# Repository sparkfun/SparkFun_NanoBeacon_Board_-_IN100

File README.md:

SparkFun NanoBeacon Board - IN100
====================================
<table class="table table-hover table-striped table-bordered">
  <tr align="center">
    <td></td>
    <td></td>
   </tr>
   <tr align="center">
    <td><a href="https://www.sparkfun.com/products/21327">SparkFun NanoBeacon Board - IN100</a></td>
    <td><a href="https://www.sparkfun.com/products/21293">SparkFun NanoBeacon Lite Board - IN100
   </tr>
</table>

The [SparkFun NanoBeacon Board - IN100](https://www.sparkfun.com/products/21327) and [SparkFun NanoBeacon Lite Board - IN100](https://www.sparkfun.com/products/21293) offer a 2.4 GHz wireless low energy BT beacon breakout with exceptional low power consumption features and minimal programming required. The board features the IN100 NanoBeacon<sup>&trade;</sup> from InPlay<sup>&trade;</sup>. The IN100 SoC is compliant with several standard 2.4 GHz protocols and has several built-in configurable features for device behavior that can drastically reduce power consumption allowing for continuous operation in the field for multiple years even with a connected device. The two versions all for users to prototype with the Lite (Development) version and then employ the standard (Production) version in large installation once your hardware and software design is complete. The board features the IN100 NanoBeacon<sup>&trade;</sup> from InPlay<sup>&trade;</sup>. The NanoBeacon config tool allows for software-free programming of the modules removing any need to perform any tricky programming for sending and receiving packets.

Repository Contents
-------------------

* **/Documents** - Datasheets, additional user documents
* **/Examples** - IN100 Config and Arduino example
* **/Hardware** - Eagle design files (.brd, .sch)
* **/Production** - Production panel files (.brd)

Documentation
--------------
* **[SparkFun NanoBeacon Board - IN100 Hookup Guide](https://learn.sparkfun.com/tutorials/sparkfun-nanobeacon-board---in100-hookup-guide)** - Basic Hookup Guide for the NanoBeacon boards.

Product Versions
-----------------

* [WRL-21327](https://www.sparkfun.com/products/21327) - NanoBeacon Board initial release (includes headers)
* [WRL-21293](https://www.sparkfun.com/products/21293) - NanoBeacon Lite Board initial release (includes Reset button and Power LED)

License Information
-------------------

This product is _**open source**_! 

Please review the LICENSE.md file for license information. 

If you have any questions or concerns on licensing, please contact technical support on our [SparkFun forums](https://forum.sparkfun.com/viewforum.php?f=152).

Distributed as-is; no warranty is given.

- Your friends at SparkFun.

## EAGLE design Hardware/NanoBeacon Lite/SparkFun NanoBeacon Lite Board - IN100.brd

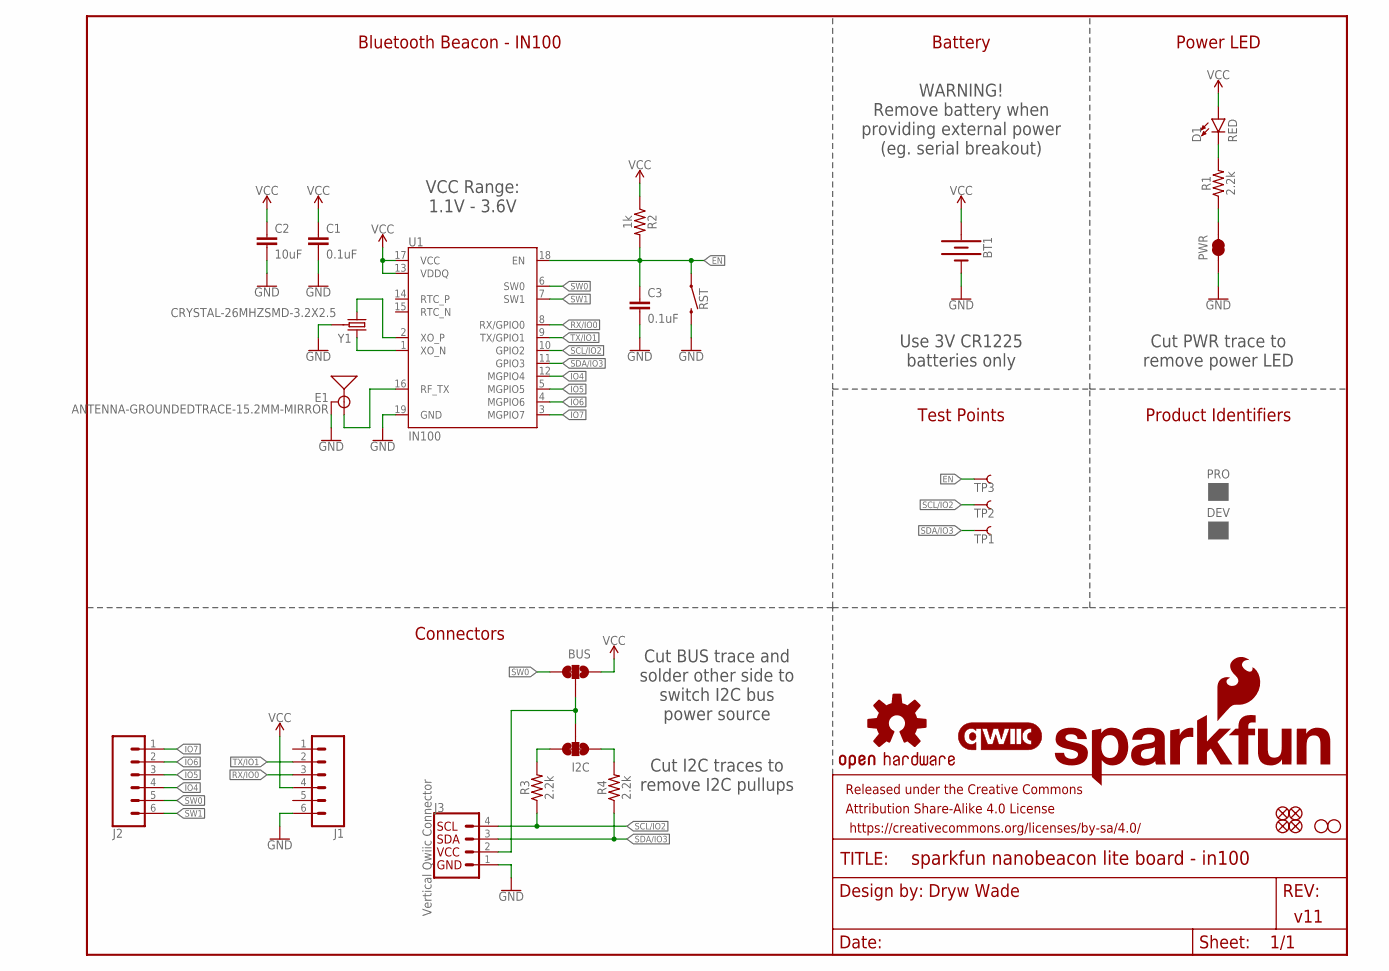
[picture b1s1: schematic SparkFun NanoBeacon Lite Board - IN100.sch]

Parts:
BT1: BATTERY-12MM_SMD_BOTH_PWR_PADS; BATTCON_12MM
BUS: JUMPER-SMT_3_1-NC_TRACE_SILK; SMT-JUMPER_3_1-NC_TRACE_SILK
C1, C3: 0.1uF; 0402-TIGHT
C2: 10uF; 0402-TIGHT
D1: RED; LED-0402
DEV: PROD_ID_PASTE_SILK; PRODUCT_IDENT_PASTE_SILK
E1: ANTENNA-GROUNDEDTRACE-15.2MM-MIRROR; TRACE_ANTENNA_2.4GHZ_15.2MM_MIRROR
FD1, FD2, FD3, FD4: FIDUCIAL1X2; FIDUCIAL-1X2
FRAME1: FRAME-LETTER; CREATIVE_COMMONS
H1, H2: STAND-OFF
I2C: JUMPER-SMT_3_2-NC_TRACE_SILK; SMT-JUMPER_3_2-NC_TRACE_SILK
J1, J2: CONN_06NO_SILK_NO_POP; 1X06_NO_SILK
J3: Vertical Qwiic Connector; JST04_1MM_VERT
LOGO1: OSHW-LOGOS; OSHW-LOGO-S
LOGO2: SFE_LOGO_NAME_FLAME.1_INCH; SFE_LOGO_NAME_FLAME_.1
LOGO3: QWIIC_LOGO_5MM; QWIIC_5MM
PRO: PROD_ID_PASTE_SILK; PRODUCT_IDENT_PASTE_SILK
PWR: JUMPER-SMT_2_NC_TRACE_SILK; SMT-JUMPER_2_NC_TRACE_SILK
R1, R3, R4: 2.2k; 0402-TIGHT
R2: 1k; 0402-TIGHT
RST: MOMENTARY-SWITCH-SPST-SMD-4.6X2.8MM; TACTILE_SWITCH_SMD_4.6X2.8MM
TP1, TP2, TP3: TEST-POINT3; PAD.03X.03
U1: IN100
Y1: CRYSTAL-26MHZSMD-3.2X2.5; CRYSTAL-SMD-3.2X2.5MM

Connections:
EN: C3.1, R2.2, RST.1, RST.2 (1), TP3.1, U1.18 (EN)
GND: BT1.GND (-), C1.2, C2.2, C3.2, E1.GND, J1.6, J3.1, PWR.1, RST.3 (2), RST.4 (2), U1.19 (GND), Y1.2 (GND), Y1.4 (GND)
IO4: J2.4, U1.12 (MGPIO4)
IO5: J2.3, U1.5 (MGPIO5)
IO6: J2.2, U1.4 (MGPIO6)
IO7: J2.1, U1.3 (MGPIO7)
unnamed: U1.1 (XO_N), Y1.3 (2)
unnamed: U1.2 (XO_P), Y1.1
unnamed: PWR.2, R1.1
unnamed: E1.ANT (SIGNAL), U1.16 (RF_TX)
unnamed: D1.C, R1.2
unnamed: I2C.1, R4.2
unnamed: BUS.2, I2C.2, J3.2
unnamed: I2C.3, R3.2
RX/IO0: J1.3, U1.8 (RX/GPIO0)
SCL/IO2: J3.4, R3.1, TP2.1, U1.10 (GPIO2)
SDA/IO3: J3.3, R4.1, TP1.1, U1.11 (GPIO3)
SW0: BUS.3, J2.5, U1.6 (SW0)
SW1: J2.6, U1.7 (SW1)
TX/IO1: J1.2, U1.9 (TX/GPIO1)
VCC: BT1.PWR@1 (+), BT1.PWR@2 (+), BUS.1, C1.1, C2.1, D1.A, J1.4, R2.1, U1.13 (VDDQ), U1.17 (VCC)

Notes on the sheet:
v11
Dryw Wade
Connectors
Battery
Bluetooth Beacon - IN100
Power LED
Cut PWR trace to remove power LED
VCC Range: 1.1V - 3.6V
Test Points
Cut I2C traces to remove I2C pullups
Cut BUS trace and solder other side to switch I2C bus power source
Use 3V CR1225 batteries only
WARNING\! Remove battery when providing external power (eg. serial breakout)
Product Identifiers

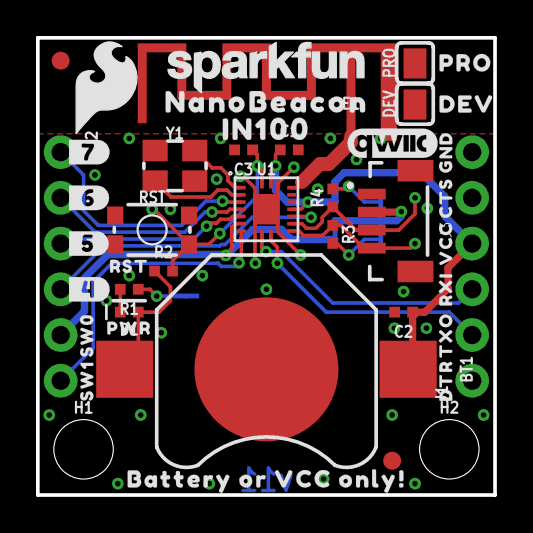
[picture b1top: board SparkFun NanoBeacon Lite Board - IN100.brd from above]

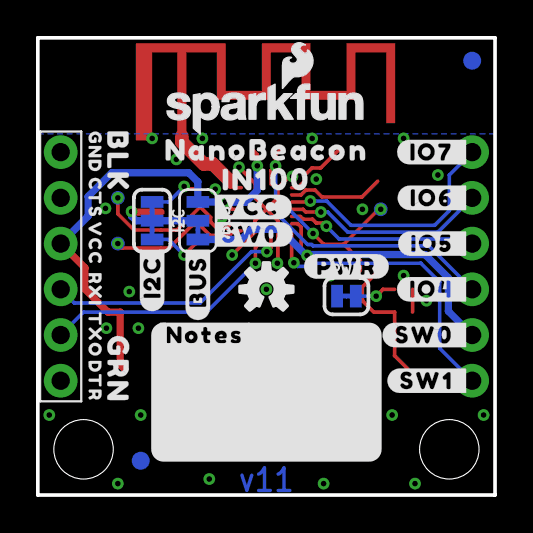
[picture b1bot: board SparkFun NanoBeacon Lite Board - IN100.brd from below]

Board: 2 copper layers, 25.4 x 25.4 mm, 63 parts (24 on the bottom side), 21 nets.

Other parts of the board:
U$1, U$29: NANOBEACON0
U$2: #_7#0
U$3: #_6#0
U$4: SFE_LOGO_NAME_.1
U$5, U$31: IN1000
U$6: #_5#0
U$7: #_4#0
U$8: SFE_LOGO_FLAME_.2
U$9: BATTERY_OR_VCC_ONLY##0
U$11: #I2C#0
U$12: #NOTES#0
U$13: #IO7_#0
U$14: #IO6_#0
U$15: #IO5_#0
U$16: #IO4_#0
U$17: #SW0_#0
U$18: #SW1_#0
U$19: #PWR#0
U$20: #SW0#3
U$21: SW00
U$22: SW10
U$23: RST0
U$24: #VCC#0
U$25: #BUS#0
U$26: PWR0
U$28: DEV0
U$30: PRO0

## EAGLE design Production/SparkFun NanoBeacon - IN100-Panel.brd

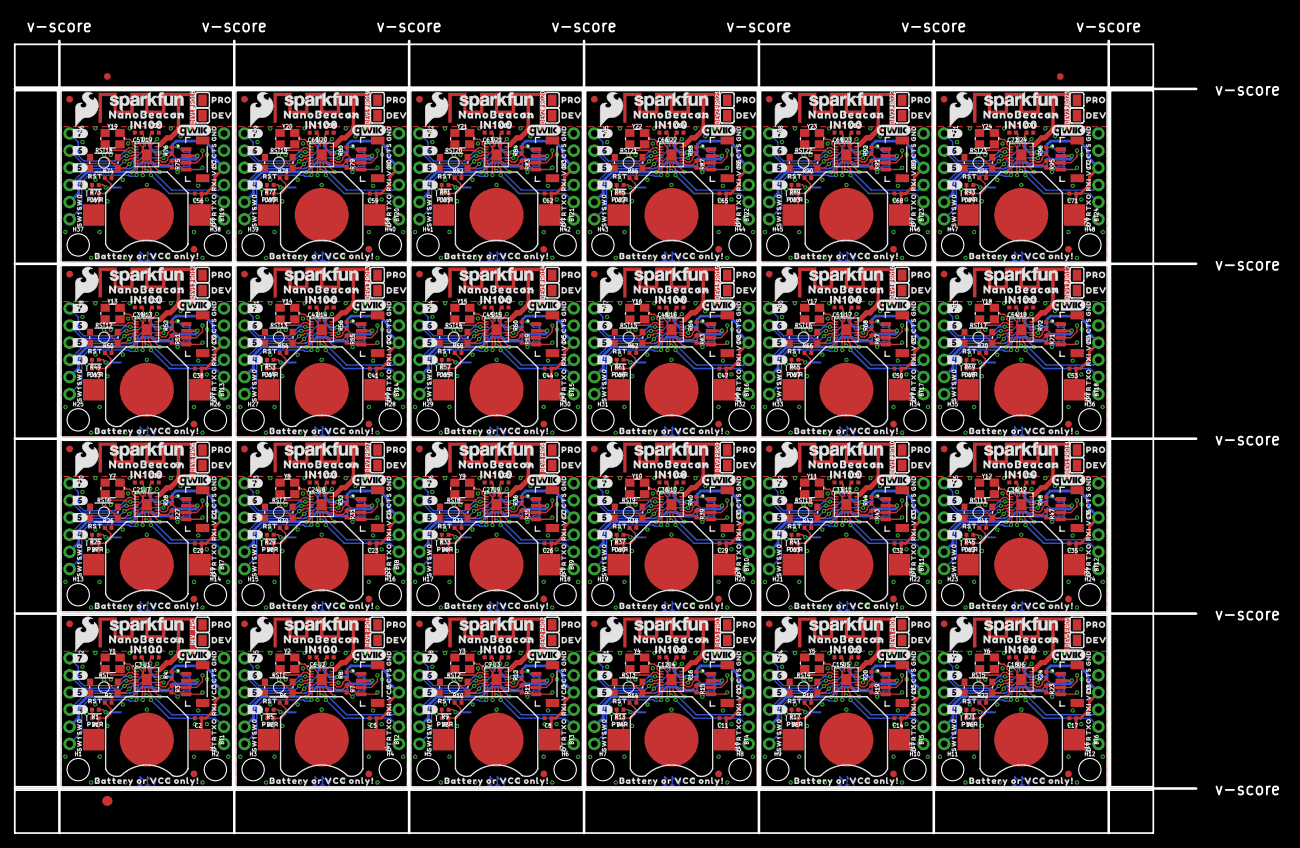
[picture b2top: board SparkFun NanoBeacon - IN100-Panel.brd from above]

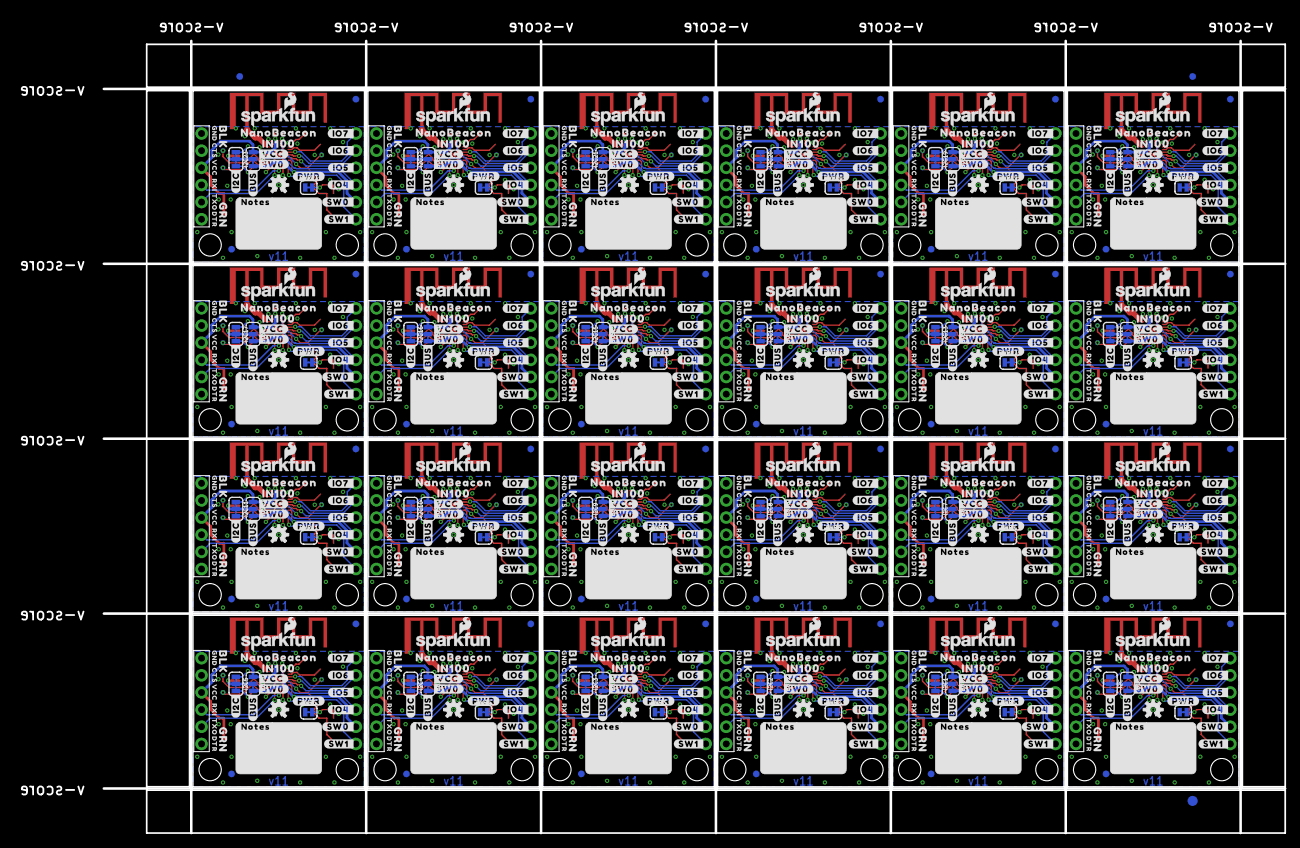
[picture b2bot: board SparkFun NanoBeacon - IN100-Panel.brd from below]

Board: 2 copper layers, 188.2 x 121.2 mm, 1494 parts (579 on the bottom side), 504 nets.

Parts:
BT1, BT2, BT3, BT4, BT5, BT6, BT7, BT8, BT9, BT10, BT11, BT12, BT13, BT14, BT15, BT16, BT17, BT18, BT19, BT20, BT21, BT22, BT23, BT24: BATTCON_12MM
BUS, BUS1, BUS2, BUS3, BUS4, BUS5, BUS6, BUS7, BUS8, BUS9, BUS10, BUS11, BUS12, BUS13, BUS14, BUS15, BUS16, BUS17, BUS18, BUS19, BUS20, BUS21, BUS22, BUS23: JUMPER-SMT_3_1-NC_TRACE_SILK; SMT-JUMPER_3_1-NC_TRACE_SILK
C1, C3, C4, C6, C7, C9, C10, C12, C13, C15, C16, C18, C19, C21, C22, C24, C25, C27, C28, C30, C31, C33, C34, C36, C37, C39, C40, C42, C43, C45, C46, C48, C49, C51, C52, C54, C55, C57, C58, C60, C61, C63, C64, C66, C67, C69, C70, C72: 0.1uF; 0402-TIGHT
C2, C5, C8, C11, C14, C17, C20, C23, C26, C29, C32, C35, C38, C41, C44, C47, C50, C53, C56, C59, C62, C65, C68, C71: 10uF; 0402-TIGHT
D1, D2, D3, D4, D5, D6, D7, D8, D9, D10, D11, D12, D13, D14, D15, D16, D17, D18, D19, D20, D21, D22, D23, D24: RED; LED-0402
DEV, DEV1, DEV2, DEV3, DEV4, DEV5, DEV6, DEV7, DEV8, DEV9, DEV10, DEV11, DEV12, DEV13, DEV14, DEV15, DEV16, DEV17, DEV18, DEV19, DEV20, DEV21, DEV22, DEV23: PROD_ID_PASTE_SILK; PRODUCT_IDENT_PASTE_SILK
E1, E2, E3, E4, E5, E6, E7, E8, E9, E10, E11, E12, E13, E14, E15, E16, E17, E18, E19, E20, E21, E22, E23, E24: ANTENNA-GROUNDEDTRACE-15.2MM; TRACE_ANTENNA_2.4GHZ_15.2MM
E$1, E$2, E$3, E$4: FIDUCIAL-1X2
E$5, E$6: FIDUCIAL-1.5X3
FD1, FD2, FD3, FD4, FD5, FD6, FD7, FD8, FD9, FD10, FD11, FD12, FD13, FD14, FD15, FD16, FD17, FD18, FD19, FD20, FD21, FD22, FD23, FD24, FD25, FD26, FD27, FD28, FD29, FD30, FD31, FD32, FD33, FD34, FD35, FD36, FD37, FD38, FD39, FD40, FD41, FD42, FD43, FD44, FD45, FD46, FD47, FD48, FD49, FD50, FD51, FD52, FD53, FD54, FD55, FD56, FD57, FD58, FD59, FD60, FD61, FD62, FD63, FD64, FD65, FD66, FD67, FD68, FD69, FD70, FD71, FD72, FD73, FD74, FD75, FD76, FD77, FD78, FD79, FD80, FD81, FD82, FD83, FD84, FD85, FD86, FD87, FD88, FD89, FD90, FD91, FD92, FD93, FD94, FD95, FD96: FIDUCIAL1X2; FIDUCIAL-1X2
H1, H2, H3, H4, H5, H6, H7, H8, H9, H10, H11, H12, H13, H14, H15, H16, H17, H18, H19, H20, H21, H22, H23, H24, H25, H26, H27, H28, H29, H30, H31, H32, H33, H34, H35, H36, H37, H38, H39, H40, H41, H42, H43, H44, H45, H46, H47, H48: STAND-OFF
I2C, I2C1, I2C2, I2C3, I2C4, I2C5, I2C6, I2C7, I2C8, I2C9, I2C10, I2C11, I2C12, I2C13, I2C14, I2C15, I2C16, I2C17, I2C18, I2C19, I2C20, I2C21, I2C22, I2C23: JUMPER-SMT_3_2-NC_TRACE_SILK; SMT-JUMPER_3_2-NC_TRACE_SILK
J1, J2, J4, J5, J7, J8, J10, J11, J13, J14, J16, J17, J19, J20, J22, J23, J25, J26, J28, J29, J31, J32, J34, J35, J37, J38, J40, J41, J43, J44, J46, J47, J49, J50, J52, J53, J55, J56, J58, J59, J61, J62, J64, J65, J67, J68, J70, J71: 1X06_NO_SILK
J3, J6, J9, J12, J15, J18, J21, J24, J27, J30, J33, J36, J39, J42, J45, J48, J51, J54, J57, J60, J63, J66, J69, J72: Vertical Qwiic Connector; JST04_1MM_VERT
LOGO1, LOGO4, LOGO7, LOGO10, LOGO13, LOGO16, LOGO19, LOGO22, LOGO25, LOGO28, LOGO31, LOGO34, LOGO37, LOGO40, LOGO43, LOGO46, LOGO49, LOGO52, LOGO55, LOGO58, LOGO61, LOGO64, LOGO67, LOGO70: OSHW-LOGOS; OSHW-LOGO-S
LOGO2, LOGO5, LOGO8, LOGO11, LOGO14, LOGO17, LOGO20, LOGO23, LOGO26, LOGO29, LOGO32, LOGO35, LOGO38, LOGO41, LOGO44, LOGO47, LOGO50, LOGO53, LOGO56, LOGO59, LOGO62, LOGO65, LOGO68, LOGO71: SFE_LOGO_NAME_FLAME.1_INCH; SFE_LOGO_NAME_FLAME_.1
LOGO3, LOGO6, LOGO9, LOGO12, LOGO15, LOGO18, LOGO21, LOGO24, LOGO27, LOGO30, LOGO33, LOGO36, LOGO39, LOGO42, LOGO45, LOGO48, LOGO51, LOGO54, LOGO57, LOGO60, LOGO63, LOGO66, LOGO69, LOGO72: QWIIC_LOGO_5MM; QWIIC_5MM
PRO, PRO1, PRO2, PRO3, PRO4, PRO5, PRO6, PRO7, PRO8, PRO9, PRO10, PRO11, PRO12, PRO13, PRO14, PRO15, PRO16, PRO17, PRO18, PRO19, PRO20, PRO21, PRO22, PRO23: PROD_ID_PASTE_SILK; PRODUCT_IDENT_PASTE_SILK
PWR, PWR1, PWR2, PWR3, PWR4, PWR5, PWR6, PWR7, PWR8, PWR9, PWR10, PWR11, PWR12, PWR13, PWR14, PWR15, PWR16, PWR17, PWR18, PWR19, PWR20, PWR21, PWR22, PWR23: JUMPER-SMT_2_NC_TRACE_SILK; SMT-JUMPER_2_NC_TRACE_SILK
R1, R3, R4, R5, R7, R8, R9, R11, R12, R13, R15, R16, R17, R19, R20, R21, R23, R24, R25, R27, R28, R29, R31, R32, R33, R35, R36, R37, R39, R40, R41, R43, R44, R45, R47, R48, R49, R51, R52, R53, R55, R56, R57, R59, R60, R61, R63, R64, R65, R67, R68, R69, R71, R72, R73, R75, R76, R77, R79, R80, R81, R83, R84, R85, R87, R88, R89, R91, R92, R93, R95, R96: 2.2k; 0402-TIGHT
R2, R6, R10, R14, R18, R22, R26, R30, R34, R38, R42, R46, R50, R54, R58, R62, R66, R70, R74, R78, R82, R86, R90, R94: 1k; 0402-TIGHT
RST, RST1, RST2, RST3, RST4, RST5, RST6, RST7, RST8, RST9, RST10, RST11, RST12, RST13, RST14, RST15, RST16, RST17, RST18, RST19, RST20, RST21, RST22, RST23: MOMENTARY-SWITCH-SPST-SMD-4.6X2.8MM; TACTILE_SWITCH_SMD_4.6X2.8MM
TP1, TP2, TP3, TP4, TP5, TP6, TP7, TP8, TP9, TP10, TP11, TP12, TP13, TP14, TP15, TP16, TP17, TP18, TP19, TP20, TP21, TP22, TP23, TP24, TP25, TP26, TP27, TP28, TP29, TP30, TP31, TP32, TP33, TP34, TP35, TP36, TP37, TP38, TP39, TP40, TP41, TP42, TP43, TP44, TP45, TP46, TP47, TP48, TP49, TP50, TP51, TP52, TP53, TP54, TP55, TP56, TP57, TP58, TP59, TP60, TP61, TP62, TP63, TP64, TP65, TP66, TP67, TP68, TP69, TP70, TP71, TP72: TEST-POINT3; PAD.03X.03
U1, U2, U3, U4, U5, U6, U7, U8, U9, U10, U11, U12, U13, U14, U15, U16, U17, U18, U19, U20, U21, U22, U23, U24: IN100
U$1, U$29, U$54, U$56, U$83, U$85, U$112, U$114, U$141, U$143, U$170, U$172, U$199, U$201, U$228, U$230, U$257, U$259, U$286, U$288, U$315, U$317, U$344, U$346, U$373, U$375, U$402, U$404, U$431, U$433, U$460, U$462, U$489, U$491, U$518, U$520, U$547, U$549, U$576, U$578, U$605, U$607, U$634, U$636, U$663, U$665, U$692, U$694: NANOBEACON0
U$2, U$27, U$60, U$89, U$118, U$147, U$176, U$205, U$234, U$263, U$292, U$321, U$350, U$379, U$408, U$437, U$466, U$495, U$524, U$553, U$582, U$611, U$640, U$669: #_7#0
U$3, U$32, U$61, U$90, U$119, U$148, U$177, U$206, U$235, U$264, U$293, U$322, U$351, U$380, U$409, U$438, U$467, U$496, U$525, U$554, U$583, U$612, U$641, U$670: #_6#0
U$4, U$10, U$59, U$88, U$117, U$146, U$175, U$204, U$233, U$262, U$291, U$320, U$349, U$378, U$407, U$436, U$465, U$494, U$523, U$552, U$581, U$610, U$639, U$668: SFE_LOGO_NAME_.1
U$5, U$31, U$55, U$57, U$84, U$86, U$113, U$115, U$142, U$144, U$171, U$173, U$200, U$202, U$229, U$231, U$258, U$260, U$287, U$289, U$316, U$318, U$345, U$347, U$374, U$376, U$403, U$405, U$432, U$434, U$461, U$463, U$490, U$492, U$519, U$521, U$548, U$550, U$577, U$579, U$606, U$608, U$635, U$637, U$664, U$666, U$693, U$695: IN1000
U$6, U$33, U$62, U$91, U$120, U$149, U$178, U$207, U$236, U$265, U$294, U$323, U$352, U$381, U$410, U$439, U$468, U$497, U$526, U$555, U$584, U$613, U$642, U$671: #_5#0
U$7, U$34, U$63, U$92, U$121, U$150, U$179, U$208, U$237, U$266, U$295, U$324, U$353, U$382, U$411, U$440, U$469, U$498, U$527, U$556, U$585, U$614, U$643, U$672: #_4#0
U$8, U$35, U$64, U$93, U$122, U$151, U$180, U$209, U$238, U$267, U$296, U$325, U$354, U$383, U$412, U$441, U$470, U$499, U$528, U$557, U$586, U$615, U$644, U$673: SFE_LOGO_FLAME_.2
U$9, U$58, U$87, U$116, U$145, U$174, U$203, U$232, U$261, U$290, U$319, U$348, U$377, U$406, U$435, U$464, U$493, U$522, U$551, U$580, U$609, U$638, U$667, U$696: BATTERY_OR_VCC_ONLY##0
U$11, U$45, U$74, U$103, U$132, U$161, U$190, U$219, U$248, U$277, U$306, U$335, U$364, U$393, U$422, U$451, U$480, U$509, U$538, U$567, U$596, U$625, U$654, U$683: #I2C#0
U$12, U$50, U$79, U$108, U$137, U$166, U$195, U$224, U$253, U$282, U$311, U$340, U$369, U$398, U$427, U$456, U$485, U$514, U$543, U$572, U$601, U$630, U$659, U$688: #NOTES#0
U$13, U$36, U$65, U$94, U$123, U$152, U$181, U$210, U$239, U$268, U$297, U$326, U$355, U$384, U$413, U$442, U$471, U$500, U$529, U$558, U$587, U$616, U$645, U$674: #IO7_#0
U$14, U$37, U$66, U$95, U$124, U$153, U$182, U$211, U$240, U$269, U$298, U$327, U$356, U$385, U$414, U$443, U$472, U$501, U$530, U$559, U$588, U$617, U$646, U$675: #IO6_#0
U$15, U$38, U$67, U$96, U$125, U$154, U$183, U$212, U$241, U$270, U$299, U$328, U$357, U$386, U$415, U$444, U$473, U$502, U$531, U$560, U$589, U$618, U$647, U$676: #IO5_#0
U$16, U$39, U$68, U$97, U$126, U$155, U$184, U$213, U$242, U$271, U$300, U$329, U$358, U$387, U$416, U$445, U$474, U$503, U$532, U$561, U$590, U$619, U$648, U$677: #IO4_#0
U$17, U$40, U$69, U$98, U$127, U$156, U$185, U$214, U$243, U$272, U$301, U$330, U$359, U$388, U$417, U$446, U$475, U$504, U$533, U$562, U$591, U$620, U$649, U$678: #SW0_#0
U$18, U$41, U$70, U$99, U$128, U$157, U$186, U$215, U$244, U$273, U$302, U$331, U$360, U$389, U$418, U$447, U$476, U$505, U$534, U$563, U$592, U$621, U$650, U$679: #SW1_#0
U$19, U$42, U$71, U$100, U$129, U$158, U$187, U$216, U$245, U$274, U$303, U$332, U$361, U$390, U$419, U$448, U$477, U$506, U$535, U$564, U$593, U$622, U$651, U$680: #PWR#0
U$20, U$46, U$75, U$104, U$133, U$162, U$191, U$220, U$249, U$278, U$307, U$336, U$365, U$394, U$423, U$452, U$481, U$510, U$539, U$568, U$597, U$626, U$655, U$684: #SW0#3
U$21, U$43, U$72, U$101, U$130, U$159, U$188, U$217, U$246, U$275, U$304, U$333, U$362, U$391, U$420, U$449, U$478, U$507, U$536, U$565, U$594, U$623, U$652, U$681: SW00
U$22, U$44, U$73, U$102, U$131, U$160, U$189, U$218, U$247, U$276, U$305, U$334, U$363, U$392, U$421, U$450, U$479, U$508, U$537, U$566, U$595, U$624, U$653, U$682: SW10
U$23, U$51, U$80, U$109, U$138, U$167, U$196, U$225, U$254, U$283, U$312, U$341, U$370, U$399, U$428, U$457, U$486, U$515, U$544, U$573, U$602, U$631, U$660, U$689: RST0
U$24, U$47, U$76, U$105, U$134, U$163, U$192, U$221, U$250, U$279, U$308, U$337, U$366, U$395, U$424, U$453, U$482, U$511, U$540, U$569, U$598, U$627, U$656, U$685: #VCC#0
U$25, U$48, U$77, U$106, U$135, U$164, U$193, U$222, U$251, U$280, U$309, U$338, U$367, U$396, U$425, U$454, U$483, U$512, U$541, U$570, U$599, U$628, U$657, U$686: #BUS#0
U$26, U$49, U$78, U$107, U$136, U$165, U$194, U$223, U$252, U$281, U$310, U$339, U$368, U$397, U$426, U$455, U$484, U$513, U$542, U$571, U$600, U$629, U$658, U$687: PWR0
U$28, U$52, U$81, U$110, U$139, U$168, U$197, U$226, U$255, U$284, U$313, U$342, U$371, U$400, U$429, U$458, U$487, U$516, U$545, U$574, U$603, U$632, U$661, U$690: DEV0
U$30, U$53, U$82, U$111, U$140, U$169, U$198, U$227, U$256, U$285, U$314, U$343, U$372, U$401, U$430, U$459, U$488, U$517, U$546, U$575, U$604, U$633, U$662, U$691: PRO0
Y1, Y2, Y3, Y4, Y5, Y6, Y7, Y8, Y9, Y10, Y11, Y12, Y13, Y14, Y15, Y16, Y17, Y18, Y19, Y20, Y21, Y22, Y23, Y24: CRYSTAL-26MHZSMD-3.2X2.5; CRYSTAL-SMD-3.2X2.5MM

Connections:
EN: C3.1, R2.2, RST.1, RST.2, TP3.1, U1.18
EN1: C6.1, R6.2, RST1.1, RST1.2, TP6.1, U2.18
EN2: C9.1, R10.2, RST2.1, RST2.2, TP9.1, U3.18
EN3: C12.1, R14.2, RST3.1, RST3.2, TP12.1, U4.18
EN4: C15.1, R18.2, RST4.1, RST4.2, TP15.1, U5.18
EN5: C18.1, R22.2, RST5.1, RST5.2, TP18.1, U6.18
EN6: C21.1, R26.2, RST6.1, RST6.2, TP21.1, U7.18
EN7: C24.1, R30.2, RST7.1, RST7.2, TP24.1, U8.18
EN8: C27.1, R34.2, RST8.1, RST8.2, TP27.1, U9.18
EN9: C30.1, R38.2, RST9.1, RST9.2, TP30.1, U10.18
EN10: C33.1, R42.2, RST10.1, RST10.2, TP33.1, U11.18
EN11: C36.1, R46.2, RST11.1, RST11.2, TP36.1, U12.18
EN12: C39.1, R50.2, RST12.1, RST12.2, TP39.1, U13.18
EN13: C42.1, R54.2, RST13.1, RST13.2, TP42.1, U14.18
EN14: C45.1, R58.2, RST14.1, RST14.2, TP45.1, U15.18
EN15: C48.1, R62.2, RST15.1, RST15.2, TP48.1, U16.18
EN16: C51.1, R66.2, RST16.1, RST16.2, TP51.1, U17.18
EN17: C54.1, R70.2, RST17.1, RST17.2, TP54.1, U18.18
EN18: C57.1, R74.2, RST18.1, RST18.2, TP57.1, U19.18
EN19: C60.1, R78.2, RST19.1, RST19.2, TP60.1, U20.18
EN20: C63.1, R82.2, RST20.1, RST20.2, TP63.1, U21.18
EN21: C66.1, R86.2, RST21.1, RST21.2, TP66.1, U22.18
EN22: C69.1, R90.2, RST22.1, RST22.2, TP69.1, U23.18
EN23: C72.1, R94.2, RST23.1, RST23.2, TP72.1, U24.18
GND: BT1.GND, C1.2, C2.2, C3.2, E1.GND, J1.6, J3.1, PWR.1, RST.3, RST.4, U1.19, Y1.2, Y1.4
GND1: BT2.GND, C4.2, C5.2, C6.2, E2.GND, J4.6, J6.1, PWR1.1, RST1.3, RST1.4, U2.19, Y2.2, Y2.4
GND2: BT3.GND, C7.2, C8.2, C9.2, E3.GND, J7.6, J9.1, PWR2.1, RST2.3, RST2.4, U3.19, Y3.2, Y3.4
GND3: BT4.GND, C10.2, C11.2, C12.2, E4.GND, J10.6, J12.1, PWR3.1, RST3.3, RST3.4, U4.19, Y4.2, Y4.4
GND4: BT5.GND, C13.2, C14.2, C15.2, E5.GND, J13.6, J15.1, PWR4.1, RST4.3, RST4.4, U5.19, Y5.2, Y5.4
GND5: BT6.GND, C16.2, C17.2, C18.2, E6.GND, J16.6, J18.1, PWR5.1, RST5.3, RST5.4, U6.19, Y6.2, Y6.4
GND6: BT7.GND, C19.2, C20.2, C21.2, E7.GND, J19.6, J21.1, PWR6.1, RST6.3, RST6.4, U7.19, Y7.2, Y7.4
GND7: BT8.GND, C22.2, C23.2, C24.2, E8.GND, J22.6, J24.1, PWR7.1, RST7.3, RST7.4, U8.19, Y8.2, Y8.4
GND8: BT9.GND, C25.2, C26.2, C27.2, E9.GND, J25.6, J27.1, PWR8.1, RST8.3, RST8.4, U9.19, Y9.2, Y9.4
GND9: BT10.GND, C28.2, C29.2, C30.2, E10.GND, J28.6, J30.1, PWR9.1, RST9.3, RST9.4, U10.19, Y10.2, Y10.4
GND10: BT11.GND, C31.2, C32.2, C33.2, E11.GND, J31.6, J33.1, PWR10.1, RST10.3, RST10.4, U11.19, Y11.2, Y11.4
GND11: BT12.GND, C34.2, C35.2, C36.2, E12.GND, J34.6, J36.1, PWR11.1, RST11.3, RST11.4, U12.19, Y12.2, Y12.4
GND12: BT13.GND, C37.2, C38.2, C39.2, E13.GND, J37.6, J39.1, PWR12.1, RST12.3, RST12.4, U13.19, Y13.2, Y13.4
GND13: BT14.GND, C40.2, C41.2, C42.2, E14.GND, J40.6, J42.1, PWR13.1, RST13.3, RST13.4, U14.19, Y14.2, Y14.4
GND14: BT15.GND, C43.2, C44.2, C45.2, E15.GND, J43.6, J45.1, PWR14.1, RST14.3, RST14.4, U15.19, Y15.2, Y15.4
GND15: BT16.GND, C46.2, C47.2, C48.2, E16.GND, J46.6, J48.1, PWR15.1, RST15.3, RST15.4, U16.19, Y16.2, Y16.4
GND16: BT17.GND, C49.2, C50.2, C51.2, E17.GND, J49.6, J51.1, PWR16.1, RST16.3, RST16.4, U17.19, Y17.2, Y17.4
GND17: BT18.GND, C52.2, C53.2, C54.2, E18.GND, J52.6, J54.1, PWR17.1, RST17.3, RST17.4, U18.19, Y18.2, Y18.4
GND18: BT19.GND, C55.2, C56.2, C57.2, E19.GND, J55.6, J57.1, PWR18.1, RST18.3, RST18.4, U19.19, Y19.2, Y19.4
GND19: BT20.GND, C58.2, C59.2, C60.2, E20.GND, J58.6, J60.1, PWR19.1, RST19.3, RST19.4, U20.19, Y20.2, Y20.4
GND20: BT21.GND, C61.2, C62.2, C63.2, E21.GND, J61.6, J63.1, PWR20.1, RST20.3, RST20.4, U21.19, Y21.2, Y21.4
GND21: BT22.GND, C64.2, C65.2, C66.2, E22.GND, J64.6, J66.1, PWR21.1, RST21.3, RST21.4, U22.19, Y22.2, Y22.4
GND22: BT23.GND, C67.2, C68.2, C69.2, E23.GND, J67.6, J69.1, PWR22.1, RST22.3, RST22.4, U23.19, Y23.2, Y23.4
GND23: BT24.GND, C70.2, C71.2, C72.2, E24.GND, J70.6, J72.1, PWR23.1, RST23.3, RST23.4, U24.19, Y24.2, Y24.4
IO1: J5.4, U2.12
IO2: J5.3, U2.5
IO3: J5.2, U2.4
IO4: J2.4, U1.12
IO5: J2.3, U1.5
IO6: J2.2, U1.4
IO7: J2.1, U1.3
IO8: J5.1, U2.3
IO9: J8.4, U3.12
IO10: J8.3, U3.5
IO11: J8.2, U3.4
IO12: J8.1, U3.3
IO13: J11.4, U4.12
IO14: J11.3, U4.5
IO15: J11.2, U4.4
IO16: J11.1, U4.3
IO17: J14.4, U5.12
IO18: J14.3, U5.5
IO19: J14.2, U5.4
IO20: J14.1, U5.3
IO21: J17.4, U6.12
IO22: J17.3, U6.5
IO23: J17.2, U6.4
IO24: J17.1, U6.3
IO25: J20.4, U7.12
IO26: J20.3, U7.5
IO27: J20.2, U7.4
IO28: J20.1, U7.3
IO29: J23.4, U8.12
IO30: J23.3, U8.5
IO31: J23.2, U8.4
IO32: J23.1, U8.3
IO33: J26.4, U9.12
IO34: J26.3, U9.5
IO35: J26.2, U9.4
IO36: J26.1, U9.3
IO37: J29.4, U10.12
IO38: J29.3, U10.5
IO39: J29.2, U10.4
IO40: J29.1, U10.3
IO41: J32.4, U11.12
IO42: J32.3, U11.5
IO43: J32.2, U11.4
IO44: J32.1, U11.3
IO45: J35.4, U12.12
IO46: J35.3, U12.5
IO47: J35.2, U12.4
IO48: J35.1, U12.3
IO49: J38.4, U13.12
IO50: J38.3, U13.5
IO51: J38.2, U13.4
IO52: J38.1, U13.3
IO53: J41.4, U14.12
IO54: J41.3, U14.5
IO55: J41.2, U14.4
IO56: J41.1, U14.3
IO57: J44.4, U15.12
IO58: J44.3, U15.5
IO59: J44.2, U15.4
IO60: J44.1, U15.3
IO61: J47.4, U16.12
IO62: J47.3, U16.5
IO63: J47.2, U16.4
IO64: J47.1, U16.3
IO65: J50.4, U17.12
IO66: J50.3, U17.5
IO67: J50.2, U17.4
IO68: J50.1, U17.3
IO69: J53.4, U18.12
IO70: J53.3, U18.5
IO71: J53.2, U18.4
IO72: J53.1, U18.3
IO73: J56.4, U19.12
IO74: J56.3, U19.5
IO75: J56.2, U19.4
IO76: J56.1, U19.3
IO77: J59.4, U20.12
IO78: J59.3, U20.5
IO79: J59.2, U20.4
IO80: J59.1, U20.3
IO81: J62.4, U21.12
IO82: J62.3, U21.5
IO83: J62.2, U21.4
IO84: J62.1, U21.3
IO85: J65.4, U22.12
IO86: J65.3, U22.5
IO87: J65.2, U22.4
IO88: J65.1, U22.3
IO89: J68.4, U23.12
IO90: J68.3, U23.5
IO91: J68.2, U23.4
IO92: J68.1, U23.3
IO93: J71.4, U24.12
IO94: J71.3, U24.5
IO95: J71.2, U24.4
IO96: J71.1, U24.3
unnamed: U1.1, Y1.3
unnamed: U1.2, Y1.1
unnamed: PWR.2, R1.1
unnamed: E1.ANT, U1.16
unnamed: D1.C, R1.2
unnamed: E2.ANT, U2.16
unnamed: I2C.1, R4.2
unnamed: BUS.2, I2C.2, J3.2
unnamed: I2C.3, R3.2
unnamed: U2.1, Y2.3
unnamed: U2.2, Y2.1
unnamed: I2C1.1, R8.2
unnamed: BUS1.2, I2C1.2, J6.2
unnamed: I2C1.3, R7.2
unnamed: PWR1.2, R5.1
unnamed: D2.C, R5.2
unnamed: E3.ANT, U3.16
unnamed: U3.1, Y3.3
unnamed: U3.2, Y3.1
unnamed: I2C2.1, R12.2
unnamed: BUS2.2, I2C2.2, J9.2
unnamed: I2C2.3, R11.2
unnamed: PWR2.2, R9.1
unnamed: D3.C, R9.2
unnamed: E4.ANT, U4.16
unnamed: U4.1, Y4.3
unnamed: U4.2, Y4.1
unnamed: I2C3.1, R16.2
unnamed: BUS3.2, I2C3.2, J12.2
unnamed: I2C3.3, R15.2
unnamed: PWR3.2, R13.1
unnamed: D4.C, R13.2
unnamed: E5.ANT, U5.16
unnamed: U5.1, Y5.3
unnamed: U5.2, Y5.1
unnamed: I2C4.1, R20.2
unnamed: BUS4.2, I2C4.2, J15.2
unnamed: I2C4.3, R19.2
unnamed: PWR4.2, R17.1
unnamed: D5.C, R17.2
unnamed: E6.ANT, U6.16
unnamed: U6.1, Y6.3
unnamed: U6.2, Y6.1
unnamed: I2C5.1, R24.2
unnamed: BUS5.2, I2C5.2, J18.2
unnamed: I2C5.3, R23.2
unnamed: PWR5.2, R21.1
unnamed: D6.C, R21.2
unnamed: E7.ANT, U7.16
unnamed: U7.1, Y7.3
unnamed: U7.2, Y7.1
unnamed: I2C6.1, R28.2
unnamed: BUS6.2, I2C6.2, J21.2
unnamed: I2C6.3, R27.2
unnamed: PWR6.2, R25.1
unnamed: D7.C, R25.2
unnamed: E8.ANT, U8.16
unnamed: U8.1, Y8.3
unnamed: U8.2, Y8.1
unnamed: I2C7.1, R32.2
unnamed: BUS7.2, I2C7.2, J24.2
unnamed: I2C7.3, R31.2
unnamed: PWR7.2, R29.1
unnamed: D8.C, R29.2
unnamed: E9.ANT, U9.16
unnamed: U9.1, Y9.3
unnamed: U9.2, Y9.1
unnamed: I2C8.1, R36.2
unnamed: BUS8.2, I2C8.2, J27.2
unnamed: I2C8.3, R35.2
unnamed: PWR8.2, R33.1
unnamed: D9.C, R33.2
unnamed: E10.ANT, U10.16
unnamed: U10.1, Y10.3
unnamed: U10.2, Y10.1
unnamed: I2C9.1, R40.2
unnamed: BUS9.2, I2C9.2, J30.2
unnamed: I2C9.3, R39.2
unnamed: PWR9.2, R37.1
unnamed: D10.C, R37.2
unnamed: E11.ANT, U11.16
unnamed: U11.1, Y11.3
unnamed: U11.2, Y11.1
unnamed: I2C10.1, R44.2
unnamed: BUS10.2, I2C10.2, J33.2
unnamed: I2C10.3, R43.2
unnamed: PWR10.2, R41.1
unnamed: D11.C, R41.2
unnamed: E12.ANT, U12.16
unnamed: U12.1, Y12.3
unnamed: U12.2, Y12.1
unnamed: I2C11.1, R48.2
unnamed: BUS11.2, I2C11.2, J36.2
unnamed: I2C11.3, R47.2
unnamed: PWR11.2, R45.1
unnamed: D12.C, R45.2
unnamed: E13.ANT, U13.16
unnamed: U13.1, Y13.3
unnamed: U13.2, Y13.1
unnamed: I2C12.1, R52.2
unnamed: BUS12.2, I2C12.2, J39.2
unnamed: I2C12.3, R51.2
unnamed: PWR12.2, R49.1
unnamed: D13.C, R49.2
unnamed: E14.ANT, U14.16
unnamed: U14.1, Y14.3
unnamed: U14.2, Y14.1
unnamed: I2C13.1, R56.2
unnamed: BUS13.2, I2C13.2, J42.2
unnamed: I2C13.3, R55.2
unnamed: PWR13.2, R53.1
unnamed: D14.C, R53.2
unnamed: E15.ANT, U15.16
unnamed: U15.1, Y15.3
unnamed: U15.2, Y15.1
unnamed: I2C14.1, R60.2
unnamed: BUS14.2, I2C14.2, J45.2
unnamed: I2C14.3, R59.2
unnamed: PWR14.2, R57.1
unnamed: D15.C, R57.2
unnamed: E16.ANT, U16.16
unnamed: U16.1, Y16.3
unnamed: U16.2, Y16.1
unnamed: I2C15.1, R64.2
unnamed: BUS15.2, I2C15.2, J48.2
unnamed: I2C15.3, R63.2
unnamed: PWR15.2, R61.1
unnamed: D16.C, R61.2
unnamed: E17.ANT, U17.16
unnamed: U17.1, Y17.3
unnamed: U17.2, Y17.1
unnamed: I2C16.1, R68.2
unnamed: BUS16.2, I2C16.2, J51.2
unnamed: I2C16.3, R67.2
unnamed: PWR16.2, R65.1
unnamed: D17.C, R65.2
unnamed: E18.ANT, U18.16
unnamed: U18.1, Y18.3
unnamed: U18.2, Y18.1
unnamed: I2C17.1, R72.2
unnamed: BUS17.2, I2C17.2, J54.2
unnamed: I2C17.3, R71.2
unnamed: PWR17.2, R69.1
unnamed: D18.C, R69.2
unnamed: E19.ANT, U19.16
unnamed: U19.1, Y19.3
unnamed: U19.2, Y19.1
unnamed: I2C18.1, R76.2
unnamed: BUS18.2, I2C18.2, J57.2
unnamed: I2C18.3, R75.2
unnamed: PWR18.2, R73.1
unnamed: D19.C, R73.2
unnamed: E20.ANT, U20.16
unnamed: U20.1, Y20.3
unnamed: U20.2, Y20.1
unnamed: I2C19.1, R80.2
unnamed: BUS19.2, I2C19.2, J60.2
unnamed: I2C19.3, R79.2
unnamed: PWR19.2, R77.1
unnamed: D20.C, R77.2
unnamed: E21.ANT, U21.16
unnamed: U21.1, Y21.3
unnamed: U21.2, Y21.1
unnamed: I2C20.1, R84.2
unnamed: BUS20.2, I2C20.2, J63.2
unnamed: I2C20.3, R83.2
unnamed: PWR20.2, R81.1
unnamed: D21.C, R81.2
unnamed: E22.ANT, U22.16
unnamed: U22.1, Y22.3
unnamed: U22.2, Y22.1
unnamed: I2C21.1, R88.2
unnamed: BUS21.2, I2C21.2, J66.2
unnamed: I2C21.3, R87.2
unnamed: PWR21.2, R85.1
unnamed: D22.C, R85.2
unnamed: E23.ANT, U23.16
unnamed: U23.1, Y23.3
unnamed: U23.2, Y23.1
unnamed: I2C22.1, R92.2
unnamed: BUS22.2, I2C22.2, J69.2
unnamed: I2C22.3, R91.2
unnamed: PWR22.2, R89.1
unnamed: D23.C, R89.2
unnamed: E24.ANT, U24.16
unnamed: U24.1, Y24.3
unnamed: U24.2, Y24.1
unnamed: I2C23.1, R96.2
unnamed: BUS23.2, I2C23.2, J72.2
unnamed: I2C23.3, R95.2
unnamed: PWR23.2, R93.1
unnamed: D24.C, R93.2
RX/IO0: J1.3, U1.8
RX/IO1: J4.3, U2.8
RX/IO2: J7.3, U3.8
RX/IO3: J10.3, U4.8
RX/IO4: J13.3, U5.8
RX/IO5: J16.3, U6.8
RX/IO6: J19.3, U7.8
RX/IO7: J22.3, U8.8
RX/IO8: J25.3, U9.8
RX/IO9: J28.3, U10.8
RX/IO10: J31.3, U11.8
RX/IO11: J34.3, U12.8
RX/IO12: J37.3, U13.8
RX/IO13: J40.3, U14.8
RX/IO14: J43.3, U15.8
RX/IO15: J46.3, U16.8
RX/IO16: J49.3, U17.8
RX/IO17: J52.3, U18.8
RX/IO18: J55.3, U19.8
RX/IO19: J58.3, U20.8
RX/IO20: J61.3, U21.8
RX/IO21: J64.3, U22.8
RX/IO22: J67.3, U23.8
RX/IO23: J70.3, U24.8
SCL/IO1: J6.4, R7.1, TP5.1, U2.10
SCL/IO2: J3.4, R3.1, TP2.1, U1.10
SCL/IO3: J9.4, R11.1, TP8.1, U3.10
SCL/IO4: J12.4, R15.1, TP11.1, U4.10
SCL/IO5: J15.4, R19.1, TP14.1, U5.10
SCL/IO6: J18.4, R23.1, TP17.1, U6.10
SCL/IO7: J21.4, R27.1, TP20.1, U7.10
SCL/IO8: J24.4, R31.1, TP23.1, U8.10
SCL/IO9: J27.4, R35.1, TP26.1, U9.10
SCL/IO10: J30.4, R39.1, TP29.1, U10.10
SCL/IO11: J33.4, R43.1, TP32.1, U11.10
SCL/IO12: J36.4, R47.1, TP35.1, U12.10
SCL/IO13: J39.4, R51.1, TP38.1, U13.10
SCL/IO14: J42.4, R55.1, TP41.1, U14.10
SCL/IO15: J45.4, R59.1, TP44.1, U15.10
SCL/IO16: J48.4, R63.1, TP47.1, U16.10
SCL/IO17: J51.4, R67.1, TP50.1, U17.10
SCL/IO18: J54.4, R71.1, TP53.1, U18.10
SCL/IO19: J57.4, R75.1, TP56.1, U19.10
SCL/IO20: J60.4, R79.1, TP59.1, U20.10
SCL/IO21: J63.4, R83.1, TP62.1, U21.10
SCL/IO22: J66.4, R87.1, TP65.1, U22.10
SCL/IO23: J69.4, R91.1, TP68.1, U23.10
SCL/IO24: J72.4, R95.1, TP71.1, U24.10
SDA/IO1: J6.3, R8.1, TP4.1, U2.11
SDA/IO2: J9.3, R12.1, TP7.1, U3.11
SDA/IO3: J3.3, R4.1, TP1.1, U1.11
SDA/IO4: J12.3, R16.1, TP10.1, U4.11
SDA/IO5: J15.3, R20.1, TP13.1, U5.11
SDA/IO6: J18.3, R24.1, TP16.1, U6.11
SDA/IO7: J21.3, R28.1, TP19.1, U7.11
SDA/IO8: J24.3, R32.1, TP22.1, U8.11
SDA/IO9: J27.3, R36.1, TP25.1, U9.11
SDA/IO10: J30.3, R40.1, TP28.1, U10.11
SDA/IO11: J33.3, R44.1, TP31.1, U11.11
SDA/IO12: J36.3, R48.1, TP34.1, U12.11
SDA/IO13: J39.3, R52.1, TP37.1, U13.11
SDA/IO14: J42.3, R56.1, TP40.1, U14.11
SDA/IO15: J45.3, R60.1, TP43.1, U15.11
SDA/IO16: J48.3, R64.1, TP46.1, U16.11
SDA/IO17: J51.3, R68.1, TP49.1, U17.11
SDA/IO18: J54.3, R72.1, TP52.1, U18.11
SDA/IO19: J57.3, R76.1, TP55.1, U19.11
SDA/IO20: J60.3, R80.1, TP58.1, U20.11
SDA/IO21: J63.3, R84.1, TP61.1, U21.11
SDA/IO22: J66.3, R88.1, TP64.1, U22.11
SDA/IO23: J69.3, R92.1, TP67.1, U23.11
SDA/IO24: J72.3, R96.1, TP70.1, U24.11
SW0: BUS.3, J2.5, U1.6
SW1: J2.6, U1.7
SW2: BUS1.3, J5.5, U2.6
SW3: J5.6, U2.7
SW4: BUS2.3, J8.5, U3.6
SW5: J8.6, U3.7
SW6: BUS3.3, J11.5, U4.6
SW7: J11.6, U4.7
SW8: BUS4.3, J14.5, U5.6
SW9: J14.6, U5.7
SW10: BUS5.3, J17.5, U6.6
SW11: J17.6, U6.7
SW12: BUS6.3, J20.5, U7.6
SW13: J20.6, U7.7
SW14: BUS7.3, J23.5, U8.6
SW15: J23.6, U8.7
SW16: BUS8.3, J26.5, U9.6
SW17: J26.6, U9.7
SW18: BUS9.3, J29.5, U10.6
SW19: J29.6, U10.7
SW20: BUS10.3, J32.5, U11.6
SW21: J32.6, U11.7
SW22: BUS11.3, J35.5, U12.6
SW23: J35.6, U12.7
SW24: BUS12.3, J38.5, U13.6
SW25: J38.6, U13.7
SW26: BUS13.3, J41.5, U14.6
SW27: J41.6, U14.7
SW28: BUS14.3, J44.5, U15.6
SW29: J44.6, U15.7
SW30: BUS15.3, J47.5, U16.6
SW31: J47.6, U16.7
SW32: BUS16.3, J50.5, U17.6
SW33: J50.6, U17.7
SW34: BUS17.3, J53.5, U18.6
SW35: J53.6, U18.7
SW36: BUS18.3, J56.5, U19.6
SW37: J56.6, U19.7
SW38: BUS19.3, J59.5, U20.6
SW39: J59.6, U20.7
SW40: BUS20.3, J62.5, U21.6
SW41: J62.6, U21.7
SW42: BUS21.3, J65.5, U22.6
SW43: J65.6, U22.7
SW44: BUS22.3, J68.5, U23.6
SW45: J68.6, U23.7
SW46: BUS23.3, J71.5, U24.6
SW47: J71.6, U24.7
TX/IO1: J1.2, U1.9
TX/IO2: J4.2, U2.9
TX/IO3: J7.2, U3.9
TX/IO4: J10.2, U4.9
TX/IO5: J13.2, U5.9
TX/IO6: J16.2, U6.9
TX/IO7: J19.2, U7.9
TX/IO8: J22.2, U8.9
TX/IO9: J25.2, U9.9
TX/IO10: J28.2, U10.9
TX/IO11: J31.2, U11.9
TX/IO12: J34.2, U12.9
TX/IO13: J37.2, U13.9
TX/IO14: J40.2, U14.9
TX/IO15: J43.2, U15.9
TX/IO16: J46.2, U16.9
TX/IO17: J49.2, U17.9
TX/IO18: J52.2, U18.9
TX/IO19: J55.2, U19.9
TX/IO20: J58.2, U20.9
TX/IO21: J61.2, U21.9
TX/IO22: J64.2, U22.9
TX/IO23: J67.2, U23.9
TX/IO24: J70.2, U24.9
VCC: BT1.PWR@1, BT1.PWR@2, BUS.1, C1.1, C2.1, D1.A, J1.4, R2.1, U1.13, U1.17
VCC1: BT2.PWR@1, BT2.PWR@2, BUS1.1, C4.1, C5.1, D2.A, J4.4, R6.1, U2.13, U2.17
VCC2: BT3.PWR@1, BT3.PWR@2, BUS2.1, C7.1, C8.1, D3.A, J7.4, R10.1, U3.13, U3.17
VCC3: BT4.PWR@1, BT4.PWR@2, BUS3.1, C10.1, C11.1, D4.A, J10.4, R14.1, U4.13, U4.17
VCC4: BT5.PWR@1, BT5.PWR@2, BUS4.1, C13.1, C14.1, D5.A, J13.4, R18.1, U5.13, U5.17
VCC5: BT6.PWR@1, BT6.PWR@2, BUS5.1, C16.1, C17.1, D6.A, J16.4, R22.1, U6.13, U6.17
VCC6: BT7.PWR@1, BT7.PWR@2, BUS6.1, C19.1, C20.1, D7.A, J19.4, R26.1, U7.13, U7.17
VCC7: BT8.PWR@1, BT8.PWR@2, BUS7.1, C22.1, C23.1, D8.A, J22.4, R30.1, U8.13, U8.17
VCC8: BT9.PWR@1, BT9.PWR@2, BUS8.1, C25.1, C26.1, D9.A, J25.4, R34.1, U9.13, U9.17
VCC9: BT10.PWR@1, BT10.PWR@2, BUS9.1, C28.1, C29.1, D10.A, J28.4, R38.1, U10.13, U10.17
VCC10: BT11.PWR@1, BT11.PWR@2, BUS10.1, C31.1, C32.1, D11.A, J31.4, R42.1, U11.13, U11.17
VCC11: BT12.PWR@1, BT12.PWR@2, BUS11.1, C34.1, C35.1, D12.A, J34.4, R46.1, U12.13, U12.17
VCC12: BT13.PWR@1, BT13.PWR@2, BUS12.1, C37.1, C38.1, D13.A, J37.4, R50.1, U13.13, U13.17
VCC13: BT14.PWR@1, BT14.PWR@2, BUS13.1, C40.1, C41.1, D14.A, J40.4, R54.1, U14.13, U14.17
VCC14: BT15.PWR@1, BT15.PWR@2, BUS14.1, C43.1, C44.1, D15.A, J43.4, R58.1, U15.13, U15.17
VCC15: BT16.PWR@1, BT16.PWR@2, BUS15.1, C46.1, C47.1, D16.A, J46.4, R62.1, U16.13, U16.17
VCC16: BT17.PWR@1, BT17.PWR@2, BUS16.1, C49.1, C50.1, D17.A, J49.4, R66.1, U17.13, U17.17
VCC17: BT18.PWR@1, BT18.PWR@2, BUS17.1, C52.1, C53.1, D18.A, J52.4, R70.1, U18.13, U18.17
VCC18: BT19.PWR@1, BT19.PWR@2, BUS18.1, C55.1, C56.1, D19.A, J55.4, R74.1, U19.13, U19.17
VCC19: BT20.PWR@1, BT20.PWR@2, BUS19.1, C58.1, C59.1, D20.A, J58.4, R78.1, U20.13, U20.17
VCC20: BT21.PWR@1, BT21.PWR@2, BUS20.1, C61.1, C62.1, D21.A, J61.4, R82.1, U21.13, U21.17
VCC21: BT22.PWR@1, BT22.PWR@2, BUS21.1, C64.1, C65.1, D22.A, J64.4, R86.1, U22.13, U22.17
VCC22: BT23.PWR@1, BT23.PWR@2, BUS22.1, C67.1, C68.1, D23.A, J67.4, R90.1, U23.13, U23.17
VCC23: BT24.PWR@1, BT24.PWR@2, BUS23.1, C70.1, C71.1, D24.A, J70.4, R94.1, U24.13, U24.17

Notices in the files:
parts and their libraries:
SparkFun-RF: Licensing: Creative Commons ShareAlike 4.0 International - https://creativecommons.org/licenses/by-sa/4.0
SparkFun-Aesthetics: Released under the Creative Commons Attribution Share-Alike 4.0 License
SparkFun-Aesthetics: https://creativecommons.org/licenses/by-sa/4.0
